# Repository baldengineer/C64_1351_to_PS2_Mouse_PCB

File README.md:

PS/2 Mouse adapter to emulate a Commodore 64 1351 mouse.

The firmware for this project comes from svofski. It is located here: https://github.com/svofski/mouse1351

This PCB design is based on his original EAGLE design, which is available here: http://sensi.org/~svo/%5Bm%5Douse/.

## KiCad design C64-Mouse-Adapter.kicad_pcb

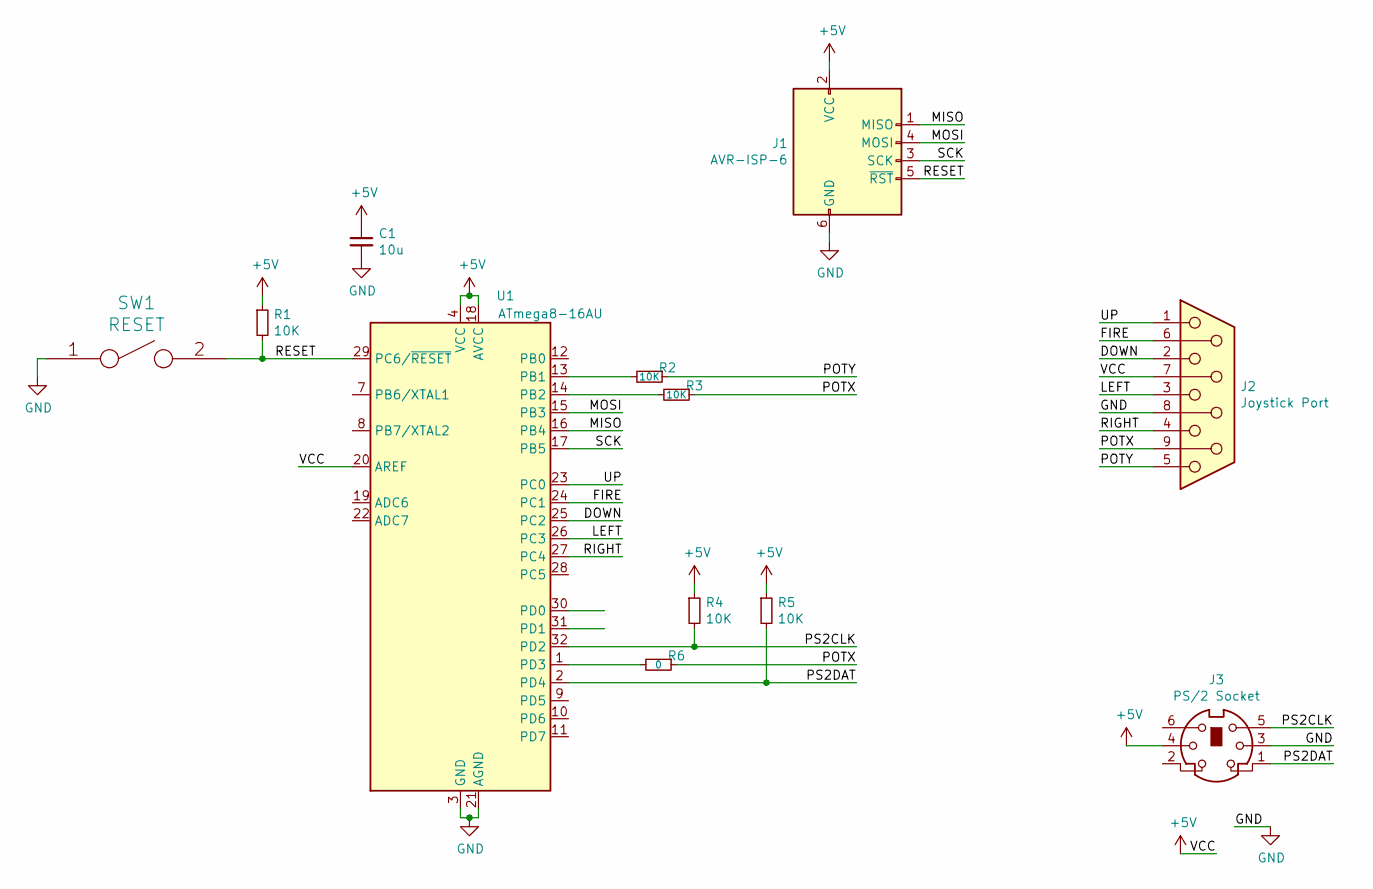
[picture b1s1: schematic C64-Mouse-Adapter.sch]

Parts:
C1: 10u; C_0805_2012Metric
J1: AVR-ISP-6; PinSocket_1x06_P2.54mm_Vertical
J2: Joystick Port; DSUB-9_Female_EdgeMount_P2.77mm
J3: PS/2 Socket; Connector_Mini-DIN_Female_6Pin_2rows
R1, R2, R3, R4, R5: 10K; R_0805_2012Metric
R6: 0; R_0805_2012Metric
SW1: RESET; Pushbutton-SMD-TL3305-2-Pad
U1: ATmega8-16AU; TQFP-32_7x7mm_P0.8mm

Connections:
+5V: C1.1, J1.2 (VCC), J2.7, J3.4, R1.1, R4.1, R5.1, U1.4 (VCC), U1.6 (VCC), U1.18 (AVCC), U1.20 (AREF)
/DOWN: J2.2, U1.25 (PC2)
/FIRE: J2.6, U1.24 (PC1)
/LEFT: J2.3, U1.26 (PC3)
/MISO: J1.1 (MISO), U1.16 (PB4)
/MOSI: J1.4 (MOSI), U1.15 (PB3)
/POTX: J2.9, R3.1, R6.1
/POTY: J2.5, R2.1
/PS2CLK: J3.5, R4.2, U1.32 (PD2)
/PS2DAT: J3.1, R5.2, U1.2 (PD4)
/RESET: J1.5 (~RST), R1.2, SW1.2, U1.29 (PC6/~RESET)
/RIGHT: J2.4, U1.27 (PC4)
/SCK: J1.3 (SCK), U1.17 (PB5)
/UP: J2.1, U1.23 (PC0)
GND: C1.2, J1.6 (GND), J2.8, J3.3, SW1.1, U1.3 (GND), U1.5 (GND), U1.21 (AGND)
unnamed: R2.2, U1.13 (PB1)
unnamed: R3.2, U1.14 (PB2)
unnamed: R6.2, U1.1 (PD3)

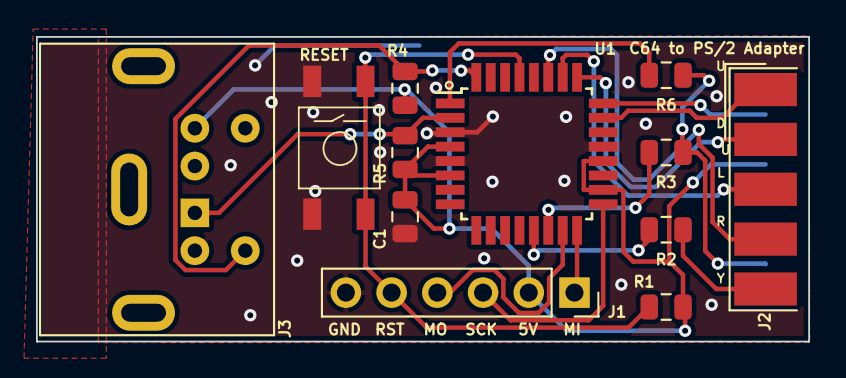
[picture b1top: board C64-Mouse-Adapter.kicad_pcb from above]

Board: 2 copper layers, 42.9 x 16.9 mm, 12 parts (0 on the bottom side), 18 nets.

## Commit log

2020-08-24 more initial
2020-09-16 Fixed DRC Problems
